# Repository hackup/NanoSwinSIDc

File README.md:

NanoSwinSIDc
============
**USE AT YOUR OWN RISK!**

The [SwinSID](http://www.swinkels.tvtom.pl/swinsid/) is a drop-in replacement for the MOS 6581 and
MOS 8580 sound chips. It is **not** fully compatible and it lacks certain
features.

The NanoSwinSIDc board layout was created using KiCAD and it is heavily based on
[the NanoSinSIDb](http://www.tolaemon.com/nss/) made by Tolaemon.

Revision 1 has been tested and can be confirmed working. Caveat: The Board/Filter labels for JP1/JP2 have accidentally been swapped!

Revision 2 features an optimized layout with standard 100mil connectors. It has not yet been tested.

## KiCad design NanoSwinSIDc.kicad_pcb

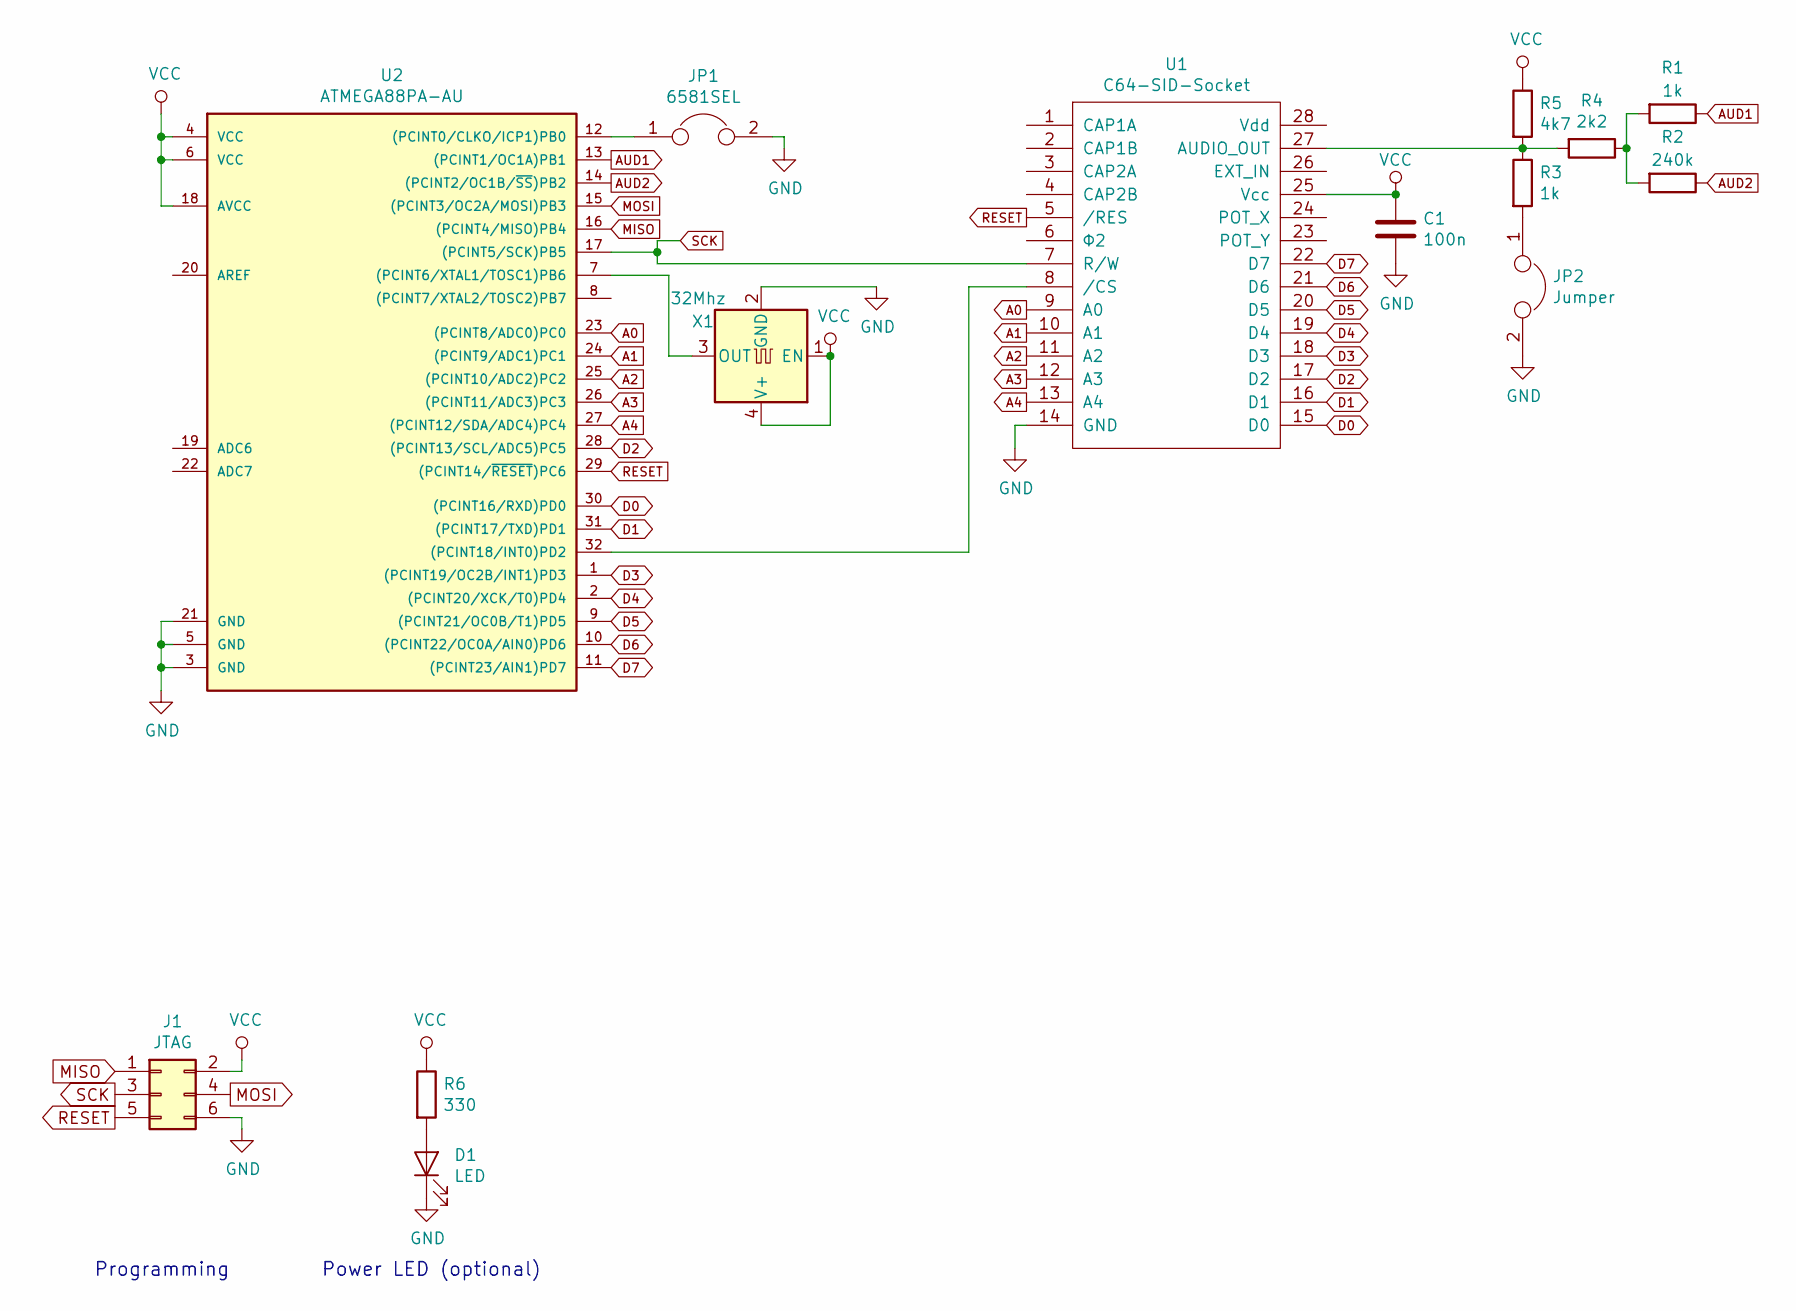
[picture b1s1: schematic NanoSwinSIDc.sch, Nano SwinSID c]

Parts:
C1: 100n; C_0805_HandSoldering
D1: LED; LED_0805_HandSoldering
J1: JTAG; Pin_Header_Straight_2x03_Pitch2.54mm
JP1: 6581SEL; Pin_Header_Angled_1x02_Pitch2.54mm
JP2: Jumper; Pin_Header_Angled_1x02_Pitch2.54mm
R1, R3: 1k; R_0805_HandSoldering
R2: 240k; R_0805_HandSoldering
R4: 2k2; R_0805_HandSoldering
R5: 4k7; R_0805_HandSoldering
R6: 330; R_0805_HandSoldering
U1: C64-SID-Socket; Socket-Adapter-DIP28
U2: ATMEGA88PA-AU; TQFP-32_7x7mm_Pitch0.8mm
X1: 32Mhz; Oscillator_SMD_EuroQuartz_XO53-4pin_5.0x3.2mm_HandSoldering

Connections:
A0: U1.9 (A0), U2.23 ((PCINT8/ADC0)PC0)
A1: U1.10 (A1), U2.24 ((PCINT9/ADC1)PC1)
A2: U1.11 (A2), U2.25 ((PCINT10/ADC2)PC2)
A3: U1.12 (A3), U2.26 ((PCINT11/ADC3)PC3)
A4: U1.13 (A4), U2.27 ((PCINT12/SDA/ADC4)PC4)
AUD1: R1.1, U2.13 ((PCINT1/OC1A)PB1)
AUD2: R2.1, U2.14 ((PCINT2/OC1B/~SS~)PB2)
D0: U1.15 (D0), U2.30 ((PCINT16/RXD)PD0)
D1: U1.16 (D1), U2.31 ((PCINT17/TXD)PD1)
D2: U1.17 (D2), U2.28 ((PCINT13/SCL/ADC5)PC5)
D3: U1.18 (D3), U2.1 ((PCINT19/OC2B/INT1)PD3)
D4: U1.19 (D4), U2.2 ((PCINT20/XCK/T0)PD4)
D5: U1.20 (D5), U2.9 ((PCINT21/OC0B/T1)PD5)
D6: U1.21 (D6), U2.10 ((PCINT22/OC0A/AIN0)PD6)
D7: U1.22 (D7), U2.11 ((PCINT23/AIN1)PD7)
GND: C1.2, D1.1 (K), J1.6, JP1.2, JP2.2, U1.14 (GND), U2.3 (GND), U2.5 (GND), U2.21 (GND), X1.2 (GND)
MISO: J1.1, U2.16 ((PCINT4/MISO)PB4)
MOSI: J1.4, U2.15 ((PCINT3/OC2A/MOSI)PB3)
unnamed: D1.2 (A), R6.2
unnamed: JP1.1, U2.12 ((PCINT0/CLKO/ICP1)PB0)
unnamed: JP2.1, R3.2
unnamed: R1.2, R2.2, R4.1
unnamed: R3.1, R4.2, R5.2, U1.27 (AUDIO_OUT)
unnamed: U1.8 (/CS), U2.32 ((PCINT18/INT0)PD2)
unnamed: U2.7 ((PCINT6/XTAL1/TOSC1)PB6), X1.3 (OUT)
RESET: J1.5, U1.5 (/RES), U2.29 ((PCINT14/~RESET~)PC6)
SCK: J1.3, U1.7 (R/W), U2.17 ((PCINT5/SCK)PB5)
VCC: C1.1, J1.2, R5.1, R6.1, U1.25 (Vcc), U2.4 (VCC), U2.6 (VCC), U2.18 (AVCC), X1.1 (EN), X1.4 (V+)

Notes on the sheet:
Power LED (optional)
Programming

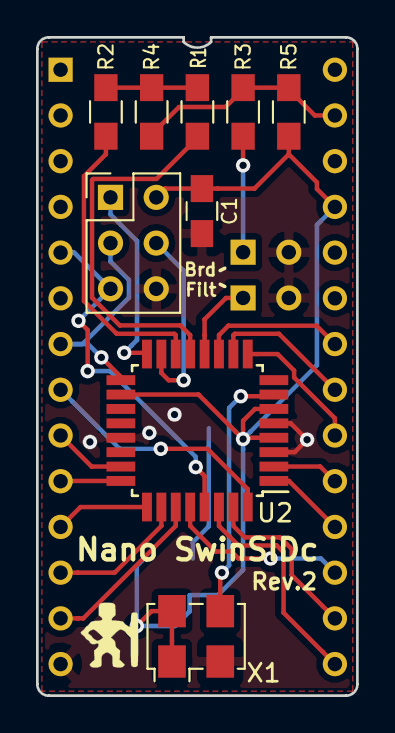
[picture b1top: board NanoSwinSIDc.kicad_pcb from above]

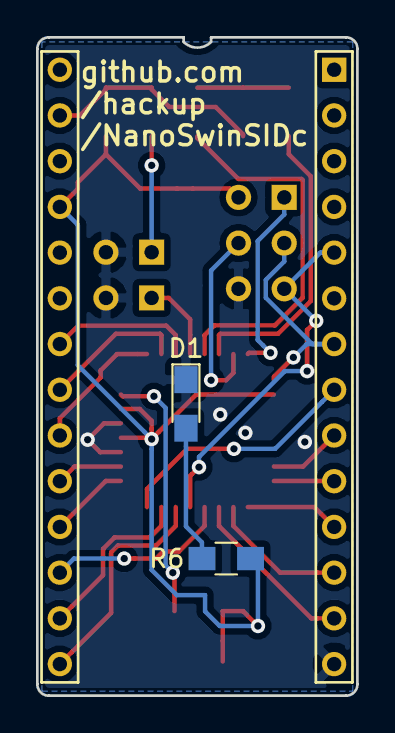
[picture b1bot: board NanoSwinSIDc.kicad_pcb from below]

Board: 2 copper layers, 17.8 x 36.6 mm, 14 parts (2 on the bottom side), 28 nets.

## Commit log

2018-04-09 Initial commit.
2018-04-12 Oscillator should have had a hand-soldering footprint.
2018-04-13 Corrected jumper labels.
2018-04-13 Added readme.
2018-04-13 Replaced 50mil header with regular 100mil ones and adapted board layout.
2019-05-12 Library update.
2019-05-12 Updated README.
